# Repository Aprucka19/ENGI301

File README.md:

# ENGI301
ENGI301 project repository

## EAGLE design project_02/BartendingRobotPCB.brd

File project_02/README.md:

# Project 2
Here are all files related to the PCB designed and manufactured for the bartending robot.

It is a 4 layer board that is approx 4 x 6.5 in

Screenshots are included showing prices of manufacturing various quantities of the board

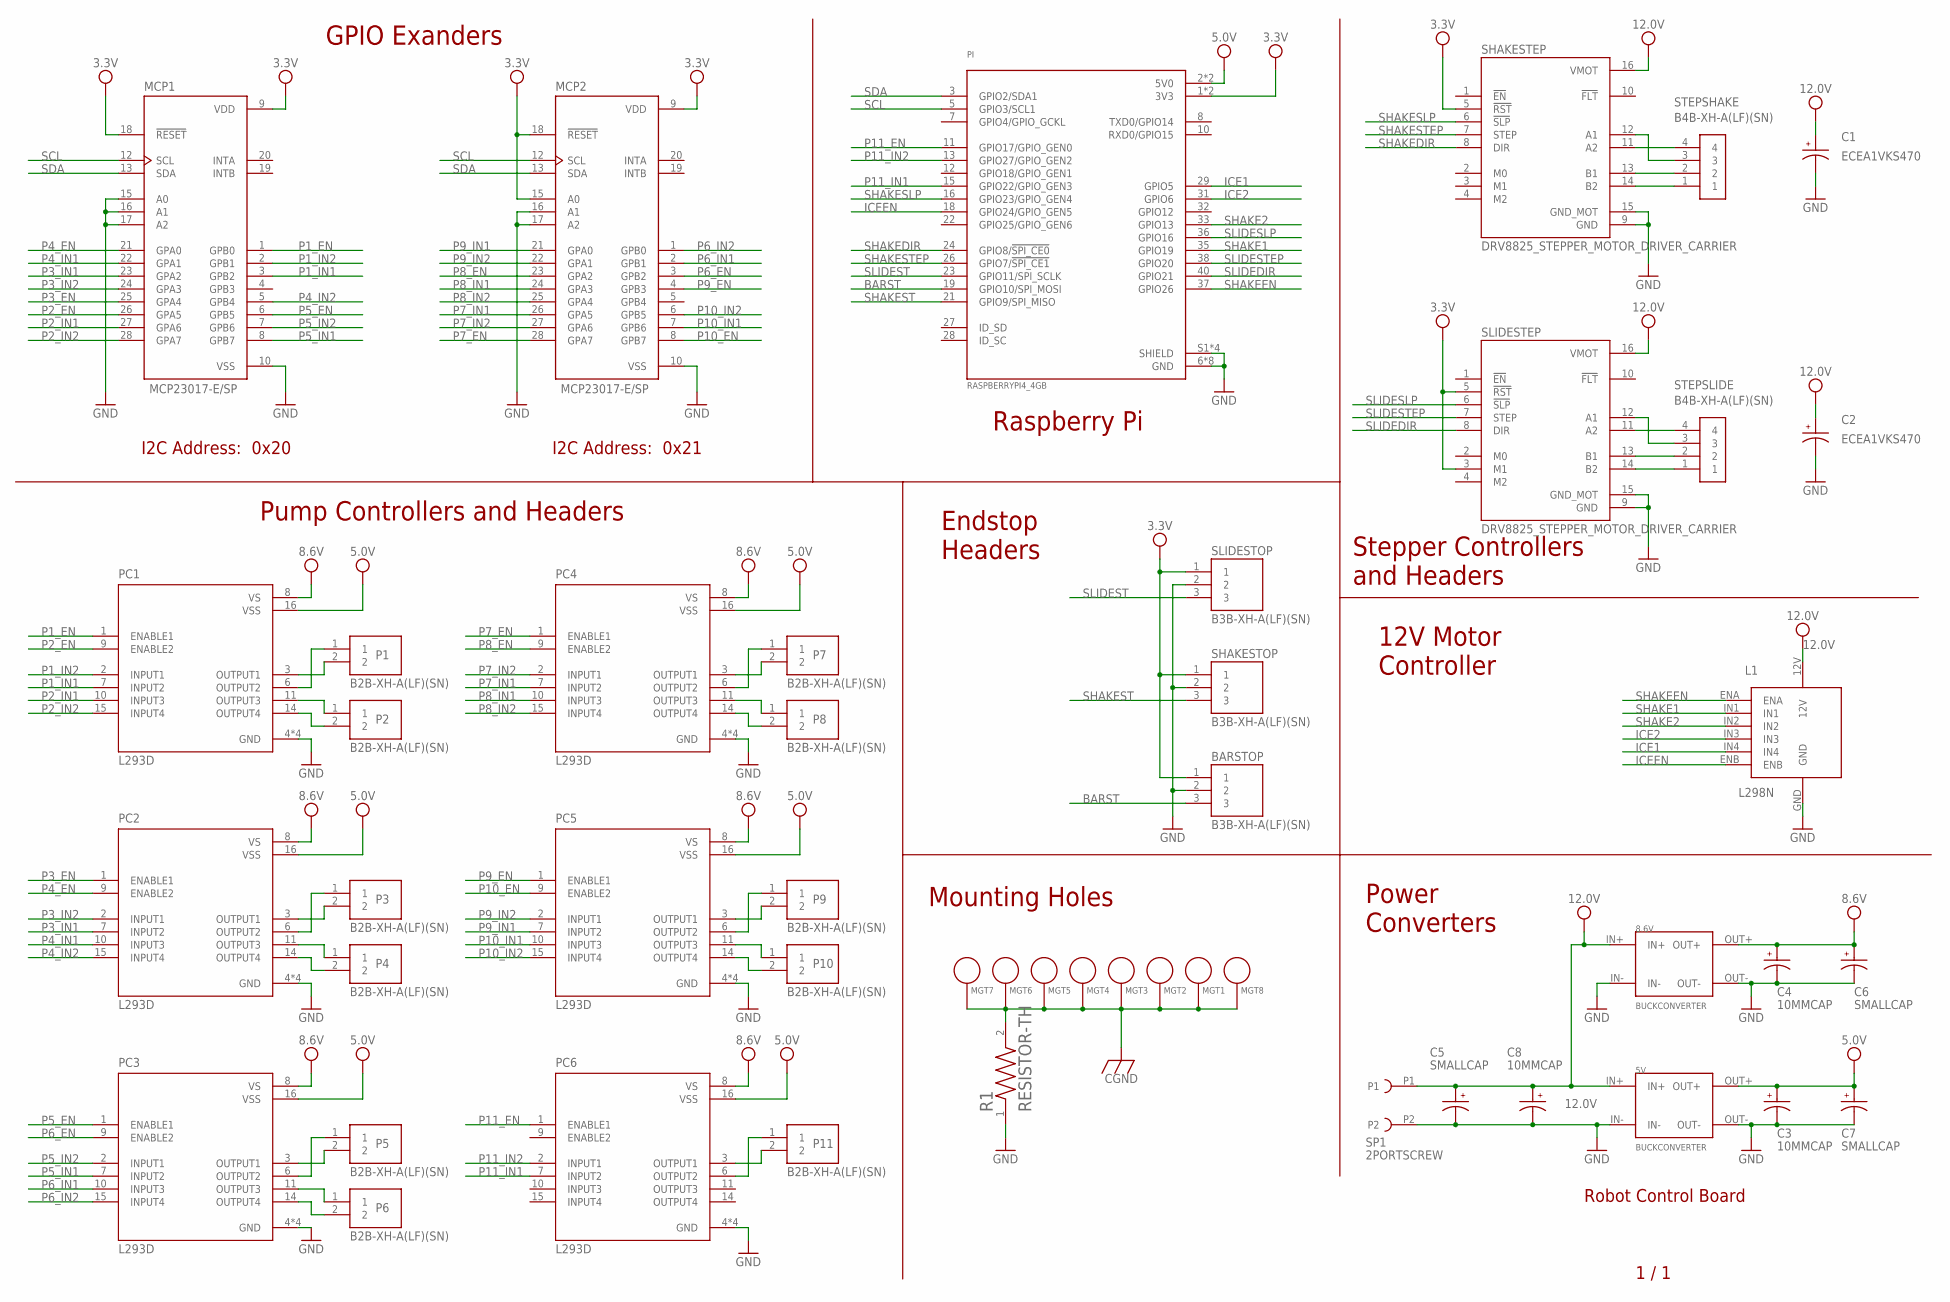
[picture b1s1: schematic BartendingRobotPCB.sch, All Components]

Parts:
5V, 8.6V: BUCKCONVERTER
BARSTOP: B3B-XH-A(LF)(SN); JST_B3B-XH-A(LF)(SN)
C1, C2: ECEA1VKS470; CAPPRD250W45D800H500
C3, C4, C8: 10MMCAP
C5, C6, C7: SMALLCAP
L1: L298N
MCP1, MCP2: MCP23017-E/SP; DIP787W45P254L3556H508Q28
MGT1, MGT2, MGT3, MGT4, MGT5, MGT6, MGT7, MGT8: MOUNTING_HOLE
P1, P2, P3, P4, P5, P6, P7, P8, P9, P10, P11: B2B-XH-A(LF)(SN); JST_B2B-XH-A(LF)(SN)
PC1, PC2, PC3, PC4, PC5, PC6: L293D; DIP880W50P254L2000H510Q16
PI: RASPBERRYPI4_4GB; MODULE_RASPBERRYPI4_4GB
R1: RESISTOR-TH; RESAD700W45L350D185
SHAKESTEP: DRV8825_STEPPER_MOTOR_DRIVER_CARRIER; IC_DRV8825_STEPPER_MOTOR_DRIVER_CARRIER
SHAKESTOP: B3B-XH-A(LF)(SN); JST_B3B-XH-A(LF)(SN)
SLIDESTEP: DRV8825_STEPPER_MOTOR_DRIVER_CARRIER; IC_DRV8825_STEPPER_MOTOR_DRIVER_CARRIER
SLIDESTOP: B3B-XH-A(LF)(SN); JST_B3B-XH-A(LF)(SN)
SP1: 2PORTSCREW
STEPSHAKE: B4B-XH-A(LF)(SN); JST_B4B-XH-A(LF)(SN)
STEPSLIDE: B4B-XH-A(LF)(SN); JST_B4B-XH-A(LF)(SN)

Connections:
3.3V: BARSTOP.1, MCP1.9 (VDD), MCP1.18 (!RESET), MCP2.9 (VDD), MCP2.15 (A0), MCP2.18 (!RESET), PI.1 (3V3), PI.17 (3V3), SHAKESTEP.5 (!RST), SHAKESTOP.1, SLIDESTEP.3 (M1), SLIDESTEP.5 (!RST), SLIDESTOP.1
5.0V: 5V.OUT+, C3.+, C7.+, PC1.16 (VSS), PC2.16 (VSS), PC3.16 (VSS), PC4.16 (VSS), PC5.16 (VSS), PC6.16 (VSS), PI.2 (5V0), PI.4 (5V0)
8.6V: 8.6V.OUT+, C4.+, C6.+, PC1.8 (VS), PC2.8 (VS), PC3.8 (VS), PC4.8 (VS), PC5.8 (VS), PC6.8 (VS)
12.0V: 5V.IN+, 8.6V.IN+, C1.P, C2.P, C5.+, C8.+, L1.12V, SHAKESTEP.16 (VMOT), SLIDESTEP.16 (VMOT), SP1.P1
BARST: BARSTOP.3, PI.19 (GPIO10/SPI_MOSI)
CGND: MGT1.P$1, MGT2.P$1, MGT3.P$1, MGT4.P$1, MGT5.P$1, MGT6.P$1, MGT7.P$1, MGT8.P$1, R1.2
GND: 5V.IN-, 5V.OUT-, 8.6V.IN-, 8.6V.OUT-, BARSTOP.2, C1.N, C2.N, C3.- (N), C4.- (N), C5.- (N), C6.- (N), C7.- (N), C8.- (N), L1.GND, MCP1.10 (VSS), MCP1.15 (A0), MCP1.16 (A1), MCP1.17 (A2), MCP2.10 (VSS), MCP2.16 (A1), MCP2.17 (A2), PC1.4 (GND), PC1.5 (GND), PC1.12 (GND), PC1.13 (GND), PC2.4 (GND), PC2.5 (GND), PC2.12 (GND), PC2.13 (GND), PC3.4 (GND), PC3.5 (GND), PC3.12 (GND), PC3.13 (GND), PC4.4 (GND), PC4.5 (GND), PC4.12 (GND), PC4.13 (GND), PC5.4 (GND), PC5.5 (GND), PC5.12 (GND), PC5.13 (GND), PC6.4 (GND), PC6.5 (GND), PC6.12 (GND), PC6.13 (GND), PI.6 (GND), PI.9 (GND), PI.14 (GND), PI.20 (GND), PI.25 (GND), PI.30 (GND), PI.34 (GND), PI.39 (GND), PI.S1 (SHIELD), PI.S2 (SHIELD), PI.S3 (SHIELD), PI.S4 (SHIELD), R1.1, SHAKESTEP.9 (GND), SHAKESTEP.15 (GND_MOT), SHAKESTOP.2, SLIDESTEP.9 (GND), SLIDESTEP.15 (GND_MOT), SLIDESTOP.2, SP1.P2
ICE1: L1.IN4, PI.29 (GPIO5)
ICE2: L1.IN3, PI.31 (GPIO6)
ICEEN: L1.ENB, PI.18 (GPIO24/GPIO_GEN5)
unnamed: SHAKESTEP.14 (B2), STEPSHAKE.1
unnamed: SHAKESTEP.13 (B1), STEPSHAKE.2
unnamed: SHAKESTEP.11 (A2), STEPSHAKE.4
unnamed: SHAKESTEP.12 (A1), STEPSHAKE.3
unnamed: SLIDESTEP.14 (B2), STEPSLIDE.1
unnamed: SLIDESTEP.13 (B1), STEPSLIDE.2
unnamed: SLIDESTEP.11 (A2), STEPSLIDE.4
unnamed: SLIDESTEP.12 (A1), STEPSLIDE.3
unnamed: P3.1, PC2.6 (OUTPUT2)
unnamed: P3.2, PC2.3 (OUTPUT1)
unnamed: P7.1, PC4.6 (OUTPUT2)
unnamed: P7.2, PC4.3 (OUTPUT1)
unnamed: P2.1, PC1.11 (OUTPUT3)
unnamed: P2.2, PC1.14 (OUTPUT4)
unnamed: P9.1, PC5.6 (OUTPUT2)
unnamed: P9.2, PC5.3 (OUTPUT1)
unnamed: P4.1, PC2.11 (OUTPUT3)
unnamed: P4.2, PC2.14 (OUTPUT4)
unnamed: P11.1, PC6.6 (OUTPUT2)
unnamed: P11.2, PC6.3 (OUTPUT1)
unnamed: P5.1, PC3.6 (OUTPUT2)
unnamed: P6.1, PC3.11 (OUTPUT3)
unnamed: P6.2, PC3.14 (OUTPUT4)
unnamed: P5.2, PC3.3 (OUTPUT1)
unnamed: P1.1, PC1.6 (OUTPUT2)
unnamed: P1.2, PC1.3 (OUTPUT1)
unnamed: P10.2, PC5.14 (OUTPUT4)
unnamed: P10.1, PC5.11 (OUTPUT3)
unnamed: P8.2, PC4.14 (OUTPUT4)
unnamed: P8.1, PC4.11 (OUTPUT3)
P1_EN: MCP1.1 (GPB0), PC1.1 (ENABLE1)
P1_IN1: MCP1.3 (GPB2), PC1.7 (INPUT2)
P1_IN2: MCP1.2 (GPB1), PC1.2 (INPUT1)
P2_EN: MCP1.26 (GPA5), PC1.9 (ENABLE2)
P2_IN1: MCP1.27 (GPA6), PC1.10 (INPUT3)
P2_IN2: MCP1.28 (GPA7), PC1.15 (INPUT4)
P3_EN: MCP1.25 (GPA4), PC2.1 (ENABLE1)
P3_IN1: MCP1.23 (GPA2), PC2.7 (INPUT2)
P3_IN2: MCP1.24 (GPA3), PC2.2 (INPUT1)
P4_EN: MCP1.21 (GPA0), PC2.9 (ENABLE2)
P4_IN1: MCP1.22 (GPA1), PC2.10 (INPUT3)
P4_IN2: MCP1.5 (GPB4), PC2.15 (INPUT4)
P5_EN: MCP1.6 (GPB5), PC3.1 (ENABLE1)
P5_IN1: MCP1.8 (GPB7), PC3.7 (INPUT2)
P5_IN2: MCP1.7 (GPB6), PC3.2 (INPUT1)
P6_EN: MCP2.3 (GPB2), PC3.9 (ENABLE2)
P6_IN1: MCP2.2 (GPB1), PC3.10 (INPUT3)
P6_IN2: MCP2.1 (GPB0), PC3.15 (INPUT4)
P7_EN: MCP2.28 (GPA7), PC4.1 (ENABLE1)
P7_IN1: MCP2.26 (GPA5), PC4.7 (INPUT2)
P7_IN2: MCP2.27 (GPA6), PC4.2 (INPUT1)
P8_EN: MCP2.23 (GPA2), PC4.9 (ENABLE2)
P8_IN1: MCP2.24 (GPA3), PC4.10 (INPUT3)
P8_IN2: MCP2.25 (GPA4), PC4.15 (INPUT4)
P9_EN: MCP2.4 (GPB3), PC5.1 (ENABLE1)
P9_IN1: MCP2.21 (GPA0), PC5.7 (INPUT2)
P9_IN2: MCP2.22 (GPA1), PC5.2 (INPUT1)
P10_EN: MCP2.8 (GPB7), PC5.9 (ENABLE2)
P10_IN1: MCP2.7 (GPB6), PC5.10 (INPUT3)
P10_IN2: MCP2.6 (GPB5), PC5.15 (INPUT4)
P11_EN: PC6.1 (ENABLE1), PI.11 (GPIO17/GPIO_GEN0)
P11_IN1: PC6.7 (INPUT2), PI.15 (GPIO22/GPIO_GEN3)
P11_IN2: PC6.2 (INPUT1), PI.13 (GPIO27/GPIO_GEN2)
SCL: MCP1.12 (SCL), MCP2.12 (SCL), PI.5 (GPIO3/SCL1)
SDA: MCP1.13 (SDA), MCP2.13 (SDA), PI.3 (GPIO2/SDA1)
SHAKE1: L1.IN1, PI.35 (GPIO19)
SHAKE2: L1.IN2, PI.33 (GPIO13)
SHAKEDIR: PI.24 (GPIO8/!SPI_CE0!), SHAKESTEP.8 (DIR)
SHAKEEN: L1.ENA, PI.37 (GPIO26)
SHAKESLP: PI.16 (GPIO23/GPIO_GEN4), SHAKESTEP.6 (!SLP)
SHAKEST: PI.21 (GPIO9/SPI_MISO), SHAKESTOP.3
SHAKESTEP: PI.26 (GPIO7/!SPI_CE1!), SHAKESTEP.7 (STEP)
SLIDEDIR: PI.40 (GPIO21), SLIDESTEP.8 (DIR)
SLIDESLP: PI.36 (GPIO16), SLIDESTEP.6 (!SLP)
SLIDEST: PI.23 (GPIO11/SPI_SCLK), SLIDESTOP.3
SLIDESTEP: PI.38 (GPIO20), SLIDESTEP.7 (STEP)

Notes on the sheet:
Mounting Holes
GPIO Exanders
Pump Controllers and Headers
Raspberry Pi
Endstop Headers
Stepper Controllers and Headers
12V Motor Controller
Power Converters
1 / 1
Robot Control Board
I2C Address: 0x21
I2C Address: 0x20

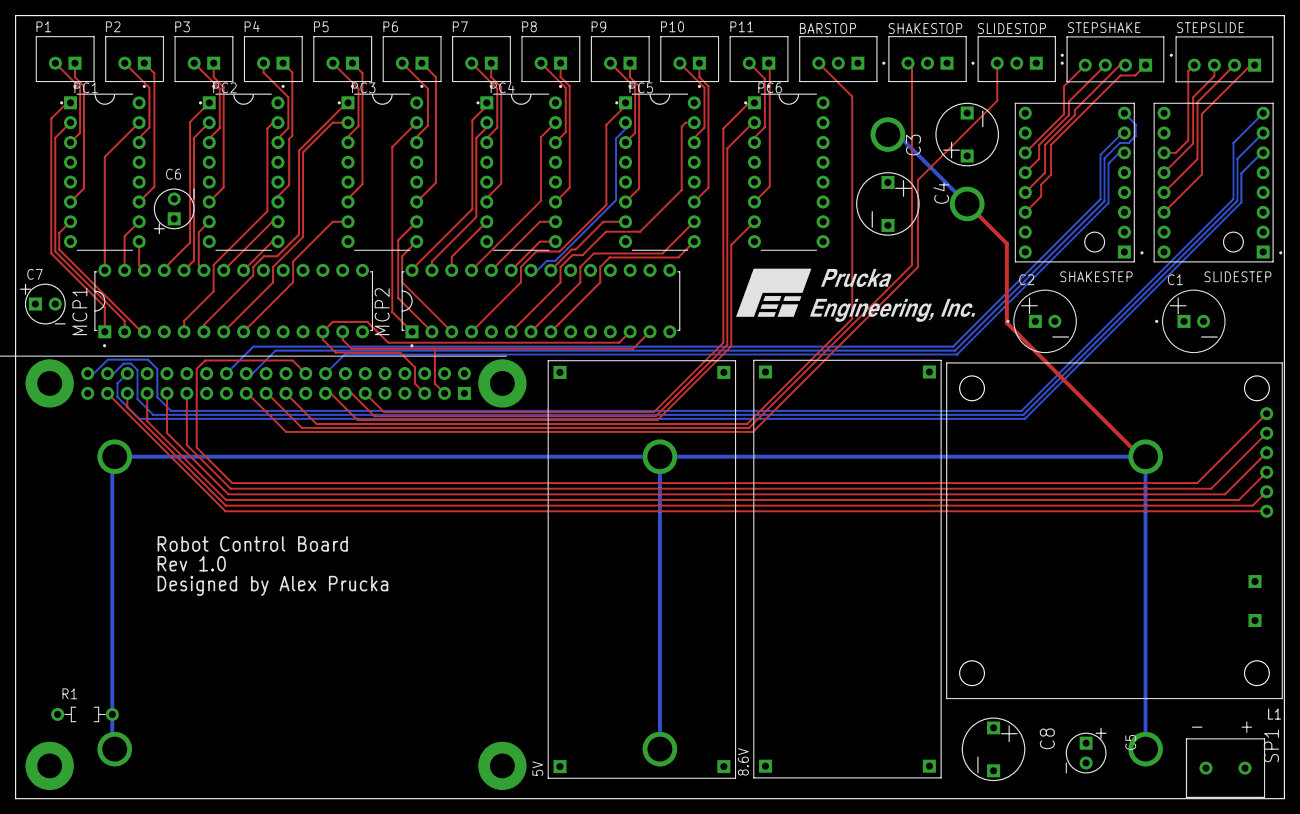
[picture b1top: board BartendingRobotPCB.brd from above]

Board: 4 copper layers, 162.6 x 100.3 mm, 48 parts (1 on the bottom side), 86 nets.

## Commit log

2022-01-27 Updating README.md
2022-02-08 initial commit before code updates
2022-02-14 finished calculator with additional features
2022-02-15 doc update on simple calc and LED blink implementation
2022-02-24 BTCode checkin
2022-02-27 all electronic components working in test stand + Optical end stop test functioning
2022-03-28 TestStandUpdate
2022-03-28 Add documentation
2022-03-28 Update documentation
2022-03-28 Create testfile
2022-03-28 Rename BTRobotCode/PythonGuiWSteppers.py to BTRobotCode/TestFiles/PythonGuiWSteppers.py
2022-03-28 Rename BTRobotCode/StepperWPWM.py to BTRobotCode/TestFiles/StepperWPWM.py
2022-03-28 Rename BTRobotCode/guiWPumps.py to BTRobotCode/TestFiles/guiWPumps.py
2022-03-28 Rename BTRobotCode/i2cTest.py to BTRobotCode/TestFiles/i2cTest.py
2022-03-28 Rename BTRobotCode/testpython.py to BTRobotCode/TestFiles/testpython.py
2022-03-28 Update Pump1 Pin Order
2022-03-28 startup pin adjustment
2022-04-02 Rename README.txt to README.md
2022-04-04 run script
2022-04-04 GPIO Expander and 11 Pump interface added
2022-04-04 Rename BTRobotCode/gpioExpanderTest.py to BTRobotCode/TestFiles/gpioExpanderTest.py
2022-04-05 Added necessary dependency installs
2022-04-05 Add Dependencies
2022-04-06 Eagle Files Added
2022-04-06 BRD/SCH upgrades
2022-04-06 cleanup
2022-04-07 update brd/sch
2022-04-08 more changes
2022-04-10 finish power and ground traces
2022-04-10 P2Proposal
2022-04-12 Added hackster link
2022-04-29 Project 2 submission
